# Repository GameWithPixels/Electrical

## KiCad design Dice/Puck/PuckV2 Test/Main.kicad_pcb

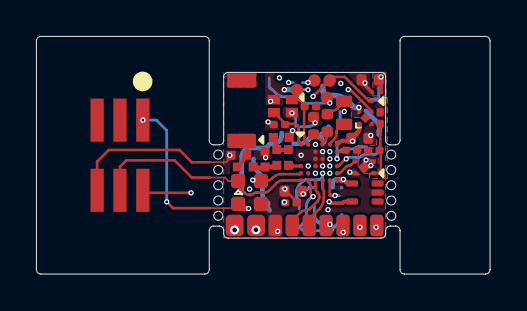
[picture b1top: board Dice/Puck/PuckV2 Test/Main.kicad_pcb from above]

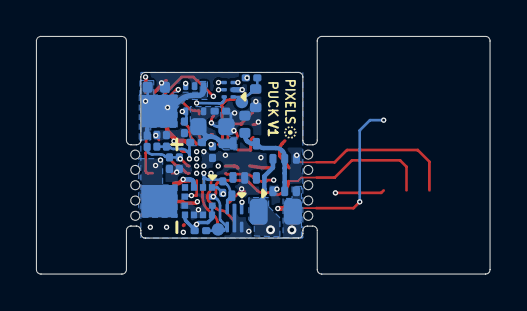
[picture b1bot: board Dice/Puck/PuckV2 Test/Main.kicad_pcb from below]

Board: 4 copper layers, 25.2 x 13.2 mm, 60 parts (28 on the bottom side), 40 nets.

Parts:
AE1: Antenna_Chip; CHIP_ANT
C1, C4, C18: 4.7uF 10V 20%; C_0402_1005Metric
C2, C5: 8pF 10V 10%; C_0201_0603Metric
C3, C10, C23: 0.1uF 10V 20%; C_0201_0603Metric
C7: 100pF NP0 10V 2%; C_0201_0603Metric
C8: 1.2pF 10V 5% C0G; 0402_RF
C9, C16: 10uF 6.3V 20%; C_0402_1005Metric
C11, C12: DNP; 0402_RF
C13: 4.7uF 25V 20%; C_0402_1005Metric
C15: 22uF 10V 20%; C_0603_1608Metric
C19: 12nF 50V 5% NP0; C_0805_2012Metric
C21, C22: 10nF 25V 10%; C_0201_0603Metric
D1: BAV99S; SOT-363_SC-70-6
J1: Conn_01x02; Batt_409090_Tabs
J2: Conn_01x04; PROG_1.27
J3: Conn_01x09; LED_CONNECTOR_9
J5: Conn_02x03_Odd_Even; PinHeader_2x03_P1.27mm_Vertical_SMD
L1: 10uH 100mA 20%; C_1.2x1.8
L2: 15nH 100mA 5%; L_0402_1005Metric
L3: 0 Ohm; 0402_RF
L4: 2.2nH 5%; 0402_RF
L5: 3.3nH 5%; 0402_RF
R1, R2, R7: 3.9M 1%; R_0201_0603Metric
R4: 10k 1%; R_0201_0603Metric
R6, R10, R11: 5.6k 1%; R_0201_0603Metric
R8: 10M 1%; R_0201_0603Metric
R9: 100k 1%; R_0201_0603Metric
R12: 510R 1%; R_0201_0603Metric
TH1: NTC 100k @ 25C; R_0402_1005Metric
U1: NRF52810-CAAA-R; WLCSP
U3: TPS715; SOT-353_SC-70-5
U4: M24C02-FMH6TG; UFDFPN5
U5: AW35122
U6: ME6230; FPB1_1-4
U7: DS6101; UDFN-4-1EP_1x1mm_P0.65mm_EP0.48x0.48mm
U8: SL1605; SOT-553
U9: XT4051; SOT-553
U10: WAS3157D-6/TR; DFN1109-6
U11: KXTJ3-1057; LGA-12_2x2mm_P0.5mm
W8: SCL; TEST_PIN
W9: SDA; TEST_PIN
W11: XC2; TEST_PIN
W15: +5V; TEST_PIN
W20: TH1; TEST_PIN
W21: LED2; TEST_PIN
W22: ADC_SELECT; TEST_PIN
W23: ADC_OUT; TEST_PIN
Y1: 32MHz 40ppm; SX16Y032000B81T001

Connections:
+5V: C15.1, R1.1, R4.1, U3.5 (VOUT), U9.5 (VCC), W15.1
+BATT: C16.1, J1.1, R7.1, R12.1, U5.A2 (VIN), U6.4 (VIN), U9.1 (BAT)
/5V_SENSE: C21.1, R1.2, R2.2, U1.D6 (P0.03/AIN1)
/ACC_INT: U1.G5 (P0.12), U11.5 (INT)
/ANTENNA: AE1.1 (FEED), C11.1, L3.2
/ANT_50: C12.1, L3.1, L5.2
/ANT_MID: C8.1, L4.2, L5.1
/ANT_NRF: L4.1, U1.E1 (ANT)
/COILA: C19.1, D1.3 (K1A2), J3.1
/COILB: C19.2, D1.6 (K3A4), J3.2
/LED_DATA: J3.4, U1.G3 (P0.16/TDATA1)
/LED_EN: U1.F3 (P0.17), U5.B2 (EN), W21.1
/LED_RETURN: J3.5, U1.G4 (P0.15)
/NTC_PHOTO_SENSE: U1.E5 (P0.04/AIN2), U10.6 (A), W23.1
/OPT_A2D: J3.8, U10.3 (B1)
/OPT_IO: J3.7, U1.F5 (P0.11)
/PROG: R6.1, U1.B5 (P0.00/XL1), U9.4 (PROG)
/SCL: R10.2, U1.G2 (P0.20/TCLK), U4.4 (SCL), U11.12 (SCL), W8.1
/SDA: R11.2, U1.F4 (P0.14), U4.3 (SDA), U11.2 (SDA), W9.1
/SENSE_SELECT: U1.E2 (P0.18/TDATA0), U10.4 (S), W22.1
/SM: U1.F6 (P0.8), U7.3 (SM)
/STATS: U1.D5 (P0.01/XL2), U9.3 (CHRG)
/VBAT_SENSE: C22.1, R7.2, R8.1, U1.E6 (P0.05/AIN3)
/Wireless Charging/B-: C23.2, J1.2, U7.2 (VSS), U7.5 (PAD)
GND: C1.2, C2.1, C3.2, C4.2, C5.1, C7.2, C8.2, C9.2, C10.2, C11.2, C12.2, C13.2, C15.2, C16.2, C18.2, C21.2, C22.2, D1.1 (A1), D1.4 (A3), J2.1, J3.3, J5.6, R2.1, R4.2, R6.2, R8.2, TH1.2, U1.B3 (VSS), U1.B4 (VSS), U1.C1 (VSS_PA), U1.D3 (VSS), U1.D4 (VSS), U1.E3 (VSS), U1.E4 (VSS), U3.2 (GND), U4.2 (VSS), U4.5 (WP), U5.B1 (GND), U6.2 (VSS), U7.4 (EB-), U8.2 (GND), U9.2 (GND), U10.2 (GND), U11.6 (GND), U11.8 (GND), U11.9 (GND), Y1.2, Y1.4
unnamed: L1.2, L2.1
unnamed: L1.1, U1.A5 (DCC)
unnamed: C3.1, U1.B6 (DEC1)
unnamed: C7.1, U1.A3 (DEC2)
unnamed: C1.1, L2.2, U1.A4 (DEC4)
unnamed: C5.2, U1.A1 (XC1), Y1.3
unnamed: C2.2, U1.A2 (XC2), W11.1, Y1.1
unnamed: U6.3 (CE), U8.5 (OUT)
unnamed: C23.1, R12.2, U7.1 (BAT)
unnamed: R9.2, TH1.1, U10.1 (B0), W20.1
SWDCLK: J2.4, J5.4, U1.G1 (SWDCLK)
SWDIO: J2.3, J5.2, U1.F1 (SWDIO)
VDC: C9.1, J3.9, R9.1, U5.A1 (VOUT), U10.5 (VCC)
VDD: C4.1, C10.1, C18.1, J2.2, J3.6, J5.1, R10.1, R11.1, U1.A6 (VDD), U1.G6 (VDD), U4.1 (VCC), U6.1 (VOUT), U8.4 (VDD), U11.1 (ADDR), U11.3 (IO_VDD), U11.7 (VDD), U11.10 (VDD), U11.11 (IO_VDD)
VEE: C13.1, D1.2 (K2), D1.5 (K4), U3.4 (VIN)

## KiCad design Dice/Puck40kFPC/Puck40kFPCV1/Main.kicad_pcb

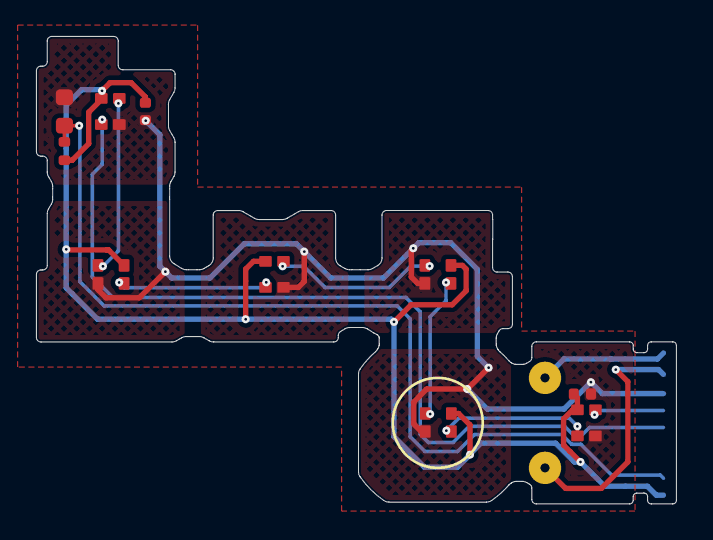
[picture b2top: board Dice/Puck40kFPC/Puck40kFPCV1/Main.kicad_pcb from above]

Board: 2 copper layers, 35.6 x 26.0 mm, 13 parts (1 on the bottom side), 12 nets.

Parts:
C10, C11: 0.1uF 10V 20%; C_0402_1005Metric
D1, D2, D3, D4, D5, D6: TX1812MJA5; TX1812MWCA5-F01
J5: Conn_01x09; LED_CONNECTOR_9
P5: COILA; TestPoint_THTPad_D1.5mm_Drill0.7mm_nosilk
P6: COILB; TestPoint_THTPad_D1.5mm_Drill0.7mm_nosilk
Q1: ZSPT-Z1608C-06F-Z4; D_0603_1608Metric
R5: 10k 1%; R_0402_1005Metric

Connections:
/COILA: J5.1, P5.1
/COILB: J5.2, P6.1
/LED_DATA: D1.3 (DIN), J5.4
/LED_RETURN: D6.1 (DOUT), J5.5
/OPT_A2D: J5.8, Q1.1 (C), R5.2
GND: C10.2, C11.2, D1.2 (GND), D2.2 (GND), D3.2 (GND), D4.2 (GND), D5.2 (GND), D6.2 (GND), J5.3, Q1.2 (E)
unnamed: D1.1 (DOUT), D2.3 (DIN)
unnamed: D2.1 (DOUT), D3.3 (DIN)
unnamed: D3.1 (DOUT), D4.3 (DIN)
unnamed: D4.1 (DOUT), D5.3 (DIN)
unnamed: D5.1 (DOUT), D6.3 (DIN)
VDC: C10.1, C11.1, D1.4 (VCC), D2.4 (VCC), D3.4 (VCC), D4.4 (VCC), D5.4 (VCC), D6.4 (VCC), J5.9, R5.1

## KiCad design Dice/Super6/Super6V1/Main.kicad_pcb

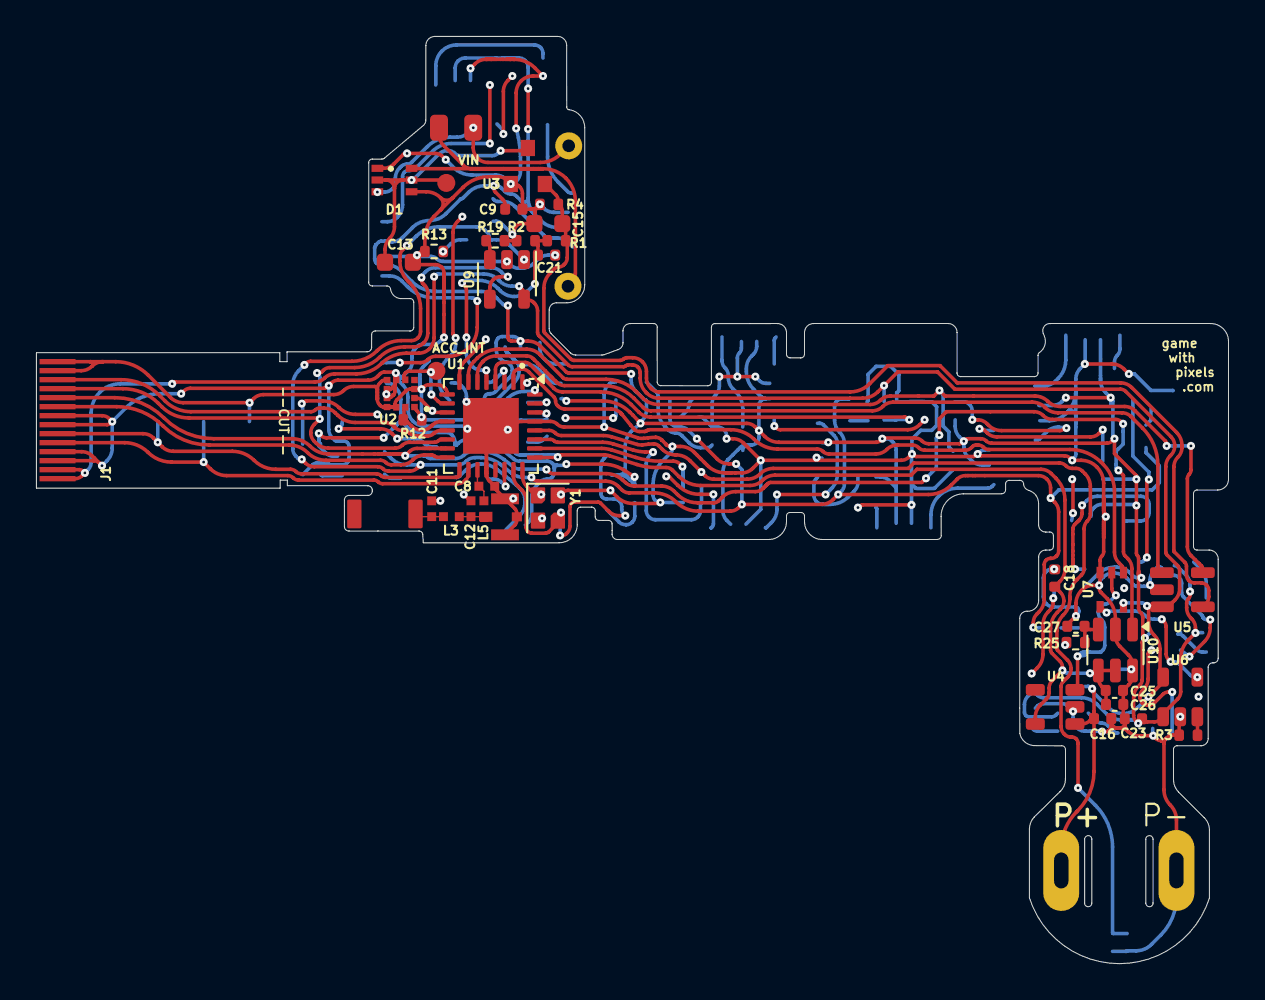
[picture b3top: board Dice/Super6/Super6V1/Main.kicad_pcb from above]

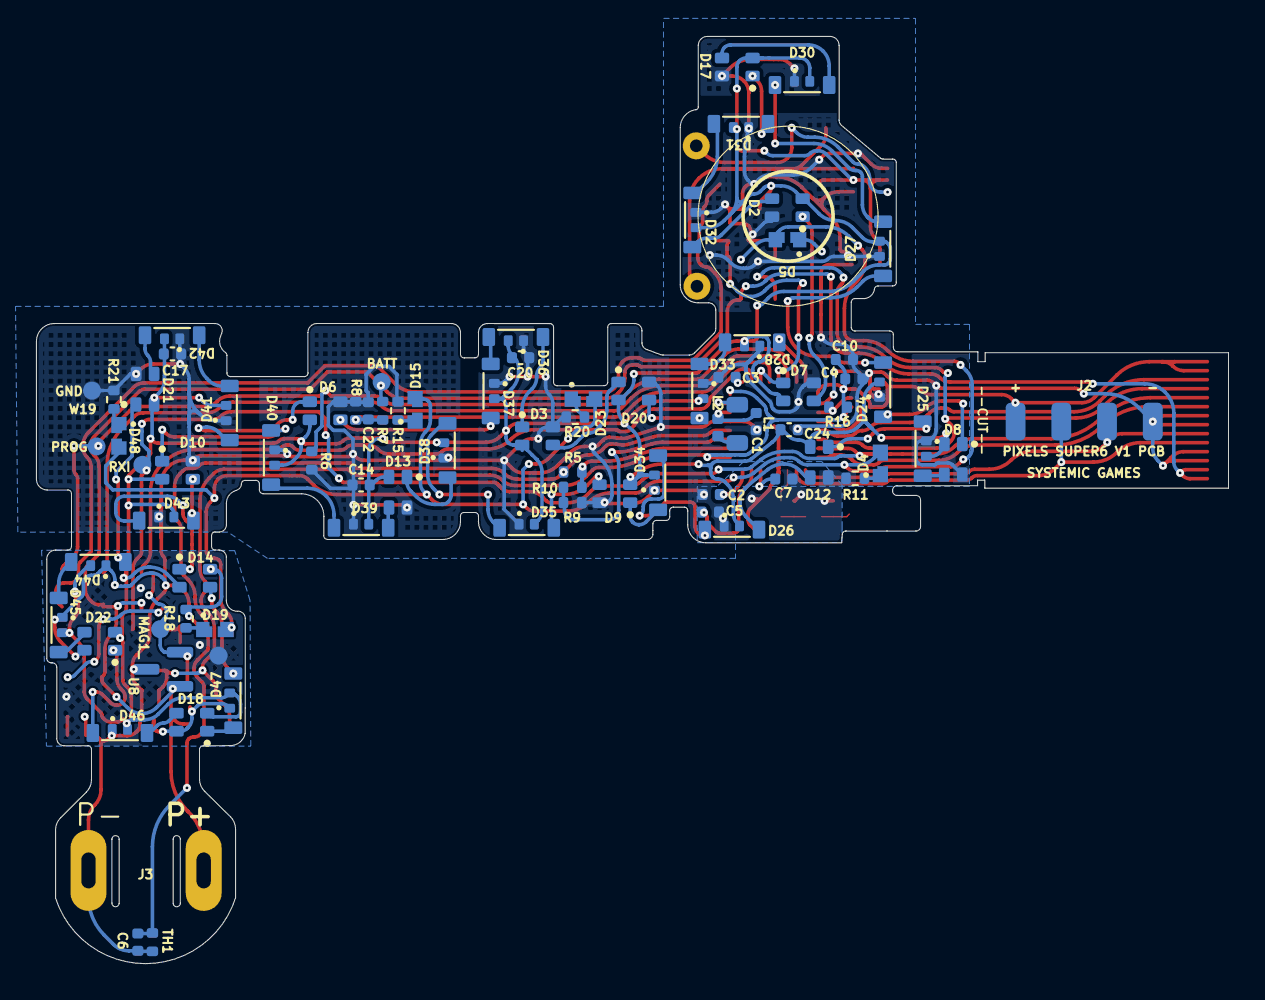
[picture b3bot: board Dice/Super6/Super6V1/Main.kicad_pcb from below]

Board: 2 copper layers, 66.2 x 51.5 mm, 123 parts (83 on the bottom side), 87 nets.

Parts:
AE2: Antenna_Chip; CHIP_ANT
C1, C4, C18: 4.7uF 10V 20%; C_0402_1005Metric
C2, C5: 8pF 10V 10%; C_0402_1005Metric
C3, C10, C14, C17, C20, C23, C24, C26: 0.1uF 10V 20%; C_0402_1005Metric
C6: DNP; C_0402_1005Metric
C7: 100pF NP0 10V 5%; C_0402_1005Metric
C8: 0.8pF 10V 5% C0G; 0402_RF
C9, C16, C25: 10uF 10V 20%; C_0402_1005Metric
C11, C12: DNP; 0402_RF
C13: 4.7uF 25V 20%; C_0603_1608Metric
C15: 22uF 10V 20%; C_0603_1608Metric
C19: 12nF 50V 5% NP0; C_0805_2012Metric
C21, C22: 10nF 25V 10%; C_0402_1005Metric
C27: 1pF 50V NP0; C_0402_1005Metric
D1: BAV99S; SOT-363_SC-70-6
D2, D3, D6, D7, D8, D9, D10, D12, D13, D14, D17, D18, D20, D21, D22: TX1812Z_2020
D4, D5, D15, D19, D23, D48: UV LED; MHP1016UVACT
D24, D25, D26, D27, D28, D30, D31, D32, D33, D34, D35, D36, D37, D38, D39, D40, D41, D42, D43, D44, D45, D46, D47: SK68XX-EC3210F
J1: Conn_01x14; FPC_14
J2: Conn_01x04; FPC-POGO-4
J3: Conn_01x02; Hongjie 10100 Connector
J4: DNP; MFH3.RECE.20369.001E.01
L1: 10uH 100mA 10%; L_0805_2012Metric
L2: 15nH 100mA 5%; L_0402_1005Metric
L3: 2.7nH 5%; 0402_RF
L5: 3.9nH 5%; 0402_RF
P5: COILA; TestPoint_THTPad_D1.5mm_Drill0.7mm_nosilk
P6: COILB; TestPoint_THTPad_D1.5mm_Drill0.7mm_nosilk
R1, R2, R7: 4.02M 1%; R_0402_1005Metric
R3, R19: 10k 5%; R_0402_1005Metric
R4, R5, R10: 100k 1%; R_0402_1005Metric
R6: 22k 1%; R_0402_1005Metric
R8: 10M 1%; R_0402_1005Metric
R9: 360k 1%; R_0402_1005Metric
R11, R13, R15, R18, R20, R21: 33R 1%; R_0402_1005Metric
R12, R16: 2.7k 5%; R_0402_1005Metric
R25: 1k 5%; R_0402_1005Metric
TH1: NTC 100k @ 25C; R_0402_1005Metric
U1: N52810_QFN32; QFN-32-1EP_5x5mm_P0.5mm_EP3.1x3.1mm
U2: KXTJ3-1057; LGA-12_2x2mm_P0.5mm
U3: PJ75BL50SA; SOT-23
U4: ME6215; SOT-23-5
U5: MCP73832T-2ACI/OT; SOT-23-5
U6, U9: MT9700; SOT-23-5
U7: SN74LVC1G08; SOT-353_SC-70-5
U8: VCS2373S; SOT-23
U10: RH6015-C; SOT-23-6
W1: RXI; TEST_PIN
W3: PROG; TEST_PIN
W6: LED_EN; TEST_PIN
W7: ACC_INT; TEST_PIN
W14: BATT; TEST_PIN
W16: VIN; TEST_PIN
W19: GND; TEST_PIN
W23: MAG1_; TEST_PIN
Y1: 32MHz 40ppm; Crystal_SMD_2016-4Pin_2.0x1.6mm

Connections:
+5V: C15.1, R1.1, R4.1, U3.2 (VOUT), U5.4 (VDD)
+BATT: C16.1, J1.1, J1.2, J3.1, R7.1, U4.1 (VIN), U5.3 (VBAT), U6.5 (VIN), U7.5 (VCC), U8.1 (VCC), U9.5 (VIN), W14.1
/5V_SENSE: C21.1, R1.2, R2.2, U1.5 (P0.05/AIN3)
/ACC_INT: U1.10 (P0.12), U2.5 (INT), W7.1
/ANTENNA: AE2.1 (FEED), C11.1, L3.2
/ANT_50: C12.1, J4.4 (RF), L3.1, L5.2
/ANT_NRF: C8.1, L5.1, U1.19 (ANT)
/BATT_NTC: C6.1, R5.2, TH1.1, U1.28 (P0.30/AIN6)
/Cap_Sense/TOUCHPAD: R25.2, W6.1
/LED_DATA: D7.1 (DIN), U1.3 (P0.01/XL2)
/LED_EN: U1.2 (P0.00/XL1), U7.1
/LEDs/LED_RETURN_6: D28.2 (DOUT), U1.8 (P0.10)
/NTC_ID_VDD: R5.1, R10.2, U1.26 (P0.25)
/PROG: R6.1, U1.7 (P0.09), U5.5 (PROG), W3.1
/Power Supply/LED_EN_OUT: U6.4 (EN), U7.4
/Power Supply/MAG1_: U4.3 (CE), U7.2, U8.2 (OUT), W23.1
/SCL: R12.2, U1.12 (P0.15), U2.12 (SCL)
/SDA: R16.2, U1.11 (P0.14), U2.2 (SDA)
/STATS: U1.6 (P0.06), U5.1 (STAT)
/UVLEDs/VUVLED: D4.2 (A), D5.2 (A), D15.2 (A), D19.2 (A), D23.2 (A), D48.2 (A), U9.1 (VOUT)
/VBAT_SENSE: C22.1, R7.2, R8.1, U1.4 (P0.04/AIN2)
GND: C1.2, C2.1, C3.2, C4.2, C5.1, C6.2, C7.2, C8.2, C9.2, C10.2, C11.2, C12.2, C13.2, C14.2, C15.2, C16.2, C17.2, C18.2, C20.2, C21.2, C22.2, C23.2, C24.2, C25.2, C26.2, C27.2, D1.1 (A1), D1.4 (A3), D2.4 (GND), D3.4 (GND), D6.4 (GND), D7.4 (GND), D8.4 (GND), D9.4 (GND), D10.4 (GND), D12.4 (GND), D13.4 (GND), D14.4 (GND), D17.4 (GND), D18.4 (GND), D20.4 (GND), D21.4 (GND), D22.4 (GND), D24.1 (GND), D25.1 (GND), D26.1 (GND), D27.1 (GND), D28.1 (GND), D30.1 (GND), D31.1 (GND), D32.1 (GND), D33.1 (GND), D34.1 (GND), D35.1 (GND), D36.1 (GND), D37.1 (GND), D38.1 (GND), D39.1 (GND), D40.1 (GND), D41.1 (GND), D42.1 (GND), D43.1 (GND), D44.1 (GND), D45.1 (GND), D46.1 (GND), D47.1 (GND), J1.3, J1.4, J1.7, J1.8, J2.4, J3.2, J4.1, J4.2, J4.3, R2.1, R3.2, R4.2, R6.2, R8.2, R9.1, R11.2, R13.2, R15.2, R18.2, R19.2, R20.2, R21.2, TH1.2, U1.20 (VSS), U1.29 (VSS), U1.33 (VSS), U2.6 (GND), U2.8 (GND), U2.9 (GND), U3.1 (VSS), U4.2 (VSS), U5.2 (VSS), U6.2 (GND), U7.3 (GND), U8.3 (GND), U9.2 (GND), U10.2 (GND), U10.6 (TOG), W19.1, Y1.2, Y1.4
unnamed: C19.2, D1.6 (K3A4), P6.1
unnamed: C19.1, D1.3 (K1A2), P5.1
unnamed: D2.1 (DIN), D7.3 (DOUT)
unnamed: D2.3 (DOUT), D32.3 (DIN)
unnamed: D3.1 (DIN), D36.2 (DOUT)
unnamed: D4.1 (K), R11.1
unnamed: D5.1 (K), R13.1
unnamed: D10.1 (DIN), D40.2 (DOUT)
unnamed: D10.3 (DOUT), D43.3 (DIN)
unnamed: D12.1 (DIN), D25.2 (DOUT)
unnamed: D12.3 (DOUT), D26.3 (DIN)
unnamed: D13.1 (DIN), D38.2 (DOUT)
unnamed: D13.3 (DOUT), D39.3 (DIN)
unnamed: D14.1 (DIN), D43.2 (DOUT)
unnamed: D14.3 (DOUT), D47.3 (DIN)
unnamed: D15.1 (K), R15.1
unnamed: D17.1 (DIN), D31.2 (DOUT)
unnamed: D17.3 (DOUT), D30.3 (DIN)
unnamed: D18.1 (DIN), D47.2 (DOUT)
unnamed: D18.3 (DOUT), D46.3 (DIN)
unnamed: D19.1 (K), R18.1
unnamed: D3.3 (DOUT), D20.1 (DIN)
unnamed: D20.3 (DOUT), D33.3 (DIN)
unnamed: D21.1 (DIN), D44.2 (DOUT)
unnamed: D21.3 (DOUT), D42.3 (DIN)
unnamed: D22.1 (DIN), D46.2 (DOUT)
unnamed: D22.3 (DOUT), D45.3 (DIN)
unnamed: D23.1 (K), R20.1
unnamed: D24.3 (DIN), D27.2 (DOUT)
unnamed: D8.1 (DIN), D24.2 (DOUT)
unnamed: D8.3 (DOUT), D25.3 (DIN)
unnamed: D26.2 (DOUT), D34.3 (DIN)
unnamed: D27.3 (DIN), D30.2 (DOUT)
unnamed: D28.3 (DIN), D33.2 (DOUT)
unnamed: D31.3 (DIN), D32.2 (DOUT)
unnamed: D9.1 (DIN), D34.2 (DOUT)
unnamed: D9.3 (DOUT), D35.3 (DIN)
unnamed: D35.2 (DOUT), D38.3 (DIN)
unnamed: D36.3 (DIN), D37.2 (DOUT)
unnamed: D6.3 (DOUT), D37.3 (DIN)
unnamed: D39.2 (DOUT), D40.3 (DIN)
unnamed: D41.3 (DIN), D42.2 (DOUT)
unnamed: D6.1 (DIN), D41.2 (DOUT)
unnamed: D44.3 (DIN), D45.2 (DOUT)
unnamed: D48.1 (K), R21.1
unnamed: L1.2, L2.1
unnamed: L1.1, U1.31 (DCC)
unnamed: C3.1, U1.1 (DEC1)
unnamed: C7.1, U1.22 (DEC3)
unnamed: C1.1, L2.2, U1.30 (DEC4)
unnamed: R9.2, R10.1, U1.27 (P0.28/AIN4)
unnamed: C5.2, U1.23 (XC1), Y1.3
unnamed: C2.2, U1.24 (XC2), Y1.1
unnamed: R3.1, U6.3 (SET)
unnamed: R19.1, U9.3 (SET)
unnamed: C27.1, R25.1, U10.3 (TCH)
RESET: J1.9, U1.16 (P0.16)
RXI: J1.10, U1.15 (P0.20/TCLK), U10.1 (OC), W1.1
SWDCLK: J1.6, J2.3, U1.17 (SWDCLK)
SWDIO: J1.5, J2.2, U1.18 (SWDIO)
SWO: J1.11, U1.14 (P0.18/TDATA0), U9.4 (EN)
TXO: J1.12, U1.13 (P0.16/TDATA1)
VDC: C9.1, C14.1, C17.1, C20.1, C23.1, C24.1, D2.2 (VCC), D3.2 (VCC), D6.2 (VCC), D7.2 (VCC), D8.2 (VCC), D9.2 (VCC), D10.2 (VCC), D12.2 (VCC), D13.2 (VCC), D14.2 (VCC), D17.2 (VCC), D18.2 (VCC), D20.2 (VCC), D21.2 (VCC), D22.2 (VCC), D24.4 (VCC), D25.4 (VCC), D26.4 (VCC), D27.4 (VCC), D28.4 (VCC), D30.4 (VCC), D31.4 (VCC), D32.4 (VCC), D33.4 (VCC), D34.4 (VCC), D35.4 (VCC), D36.4 (VCC), D37.4 (VCC), D38.4 (VCC), D39.4 (VCC), D40.4 (VCC), D41.4 (VCC), D42.4 (VCC), D43.4 (VCC), D44.4 (VCC), D45.4 (VCC), D46.4 (VCC), D47.4 (VCC), U6.1 (VOUT)
VDD: C4.1, C10.1, C18.1, C25.1, C26.1, J1.13, J1.14, J2.1, R12.1, R16.1, U1.9 (VDD), U1.25 (VDD), U1.32 (VDD), U2.1 (ADDR), U2.3 (IO_VDD), U2.7 (VDD), U2.10 (VDD), U2.11 (IO_VDD), U4.5 (VOUT), U10.4 (AHLB), U10.5 (VDD)
VEE: C13.1, D1.2 (K2), D1.5 (K4), U3.3 (VIN), W16.1

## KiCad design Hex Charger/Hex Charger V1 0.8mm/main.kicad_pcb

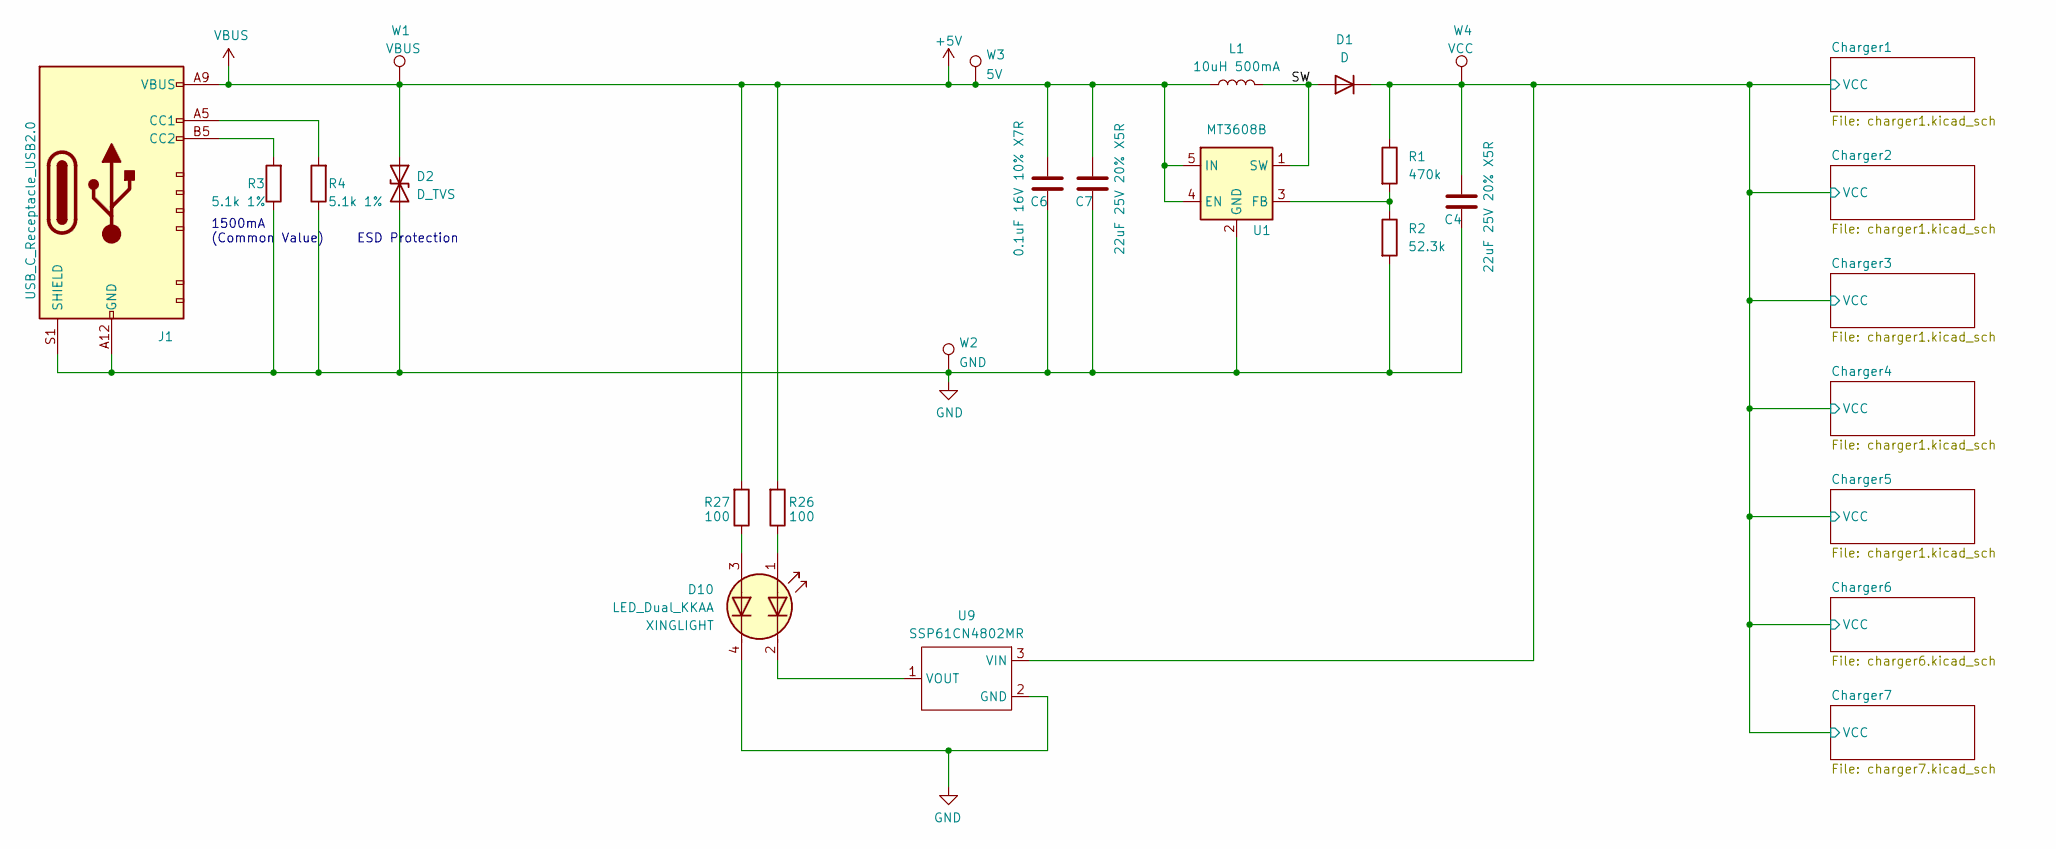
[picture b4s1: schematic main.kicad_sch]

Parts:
C4, C7: 22uF 25V 20% X5R; C_0805_2012Metric; Part Number GRM21BR61E226ME44L; LCSC Part # C86816
C6: 0.1uF 16V 10% X7R; C_0603_1608Metric; Part Number CL10B104KO8NNNC; LCSC Part # C66501
D1: D; SMAF; Part Number SS54F; LCSC Part # C908671
D2: D_TVS; DFN; Part Number LXES1UTAA1-157; LCSC Part # C5210979
D10: LED_Dual_KKAA; XL-3210SURUGC; Part Number XL-3210SURUGC; LCSC Part # C965883
J1: USB_C_Receptacle_USB2.0; USB-C-SMD_10P-P1.00-L6.8-W8.9; Part Number TYPE-C-31-M-17; LCSC Part # C283540
L1: 10uH 500mA; L_Wuerth_HCM-7050; Part Number RS0650-100MS; LCSC Part # C32712977
R1: 470k; R_0402_1005Metric; Part Number 0402WGF4703TCE; LCSC Part # C25790
R2: 52.3k; R_0402_1005Metric; Part Number 0402WGF5232TCE; LCSC Part # C26982
R3, R4: 5.1k 1%; R_0402_1005Metric; Part Number 0402WGF5101TCE; LCSC Part # C25905
R26, R27: 100; R_0402_1005Metric; Part Number 0402WGF1000TCE; LCSC Part # C25076
U1: MT3608B; SOT-23-6; Part Number MT3608B; LCSC Part # C19189893
U9: SSP61CN4802MR; SOT-23; Part Number HT7050S; LCSC Part # C2842953
W1: VBUS; TestPoint_1.5x1.5_Drill0.9mm
W2: GND; TestPoint_1.5x1.5_Drill0.9mm
W3: 5V; TestPoint_1.5x1.5_Drill0.9mm
W4: VCC; TestPoint_1.5x1.5_Drill0.9mm

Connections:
+5V: C6.1, C7.1, D2.1 (A1), J1.A9 (VBUS), J1.B9 (VBUS), L1.1, R26.2, R27.2, U1.4 (EN), U1.5 (IN), W1.1, W3.1
/Charger1/VCC: C4.1, D1.1 (K), R1.1, U9.3 (VIN), W4.1; also elsewhere on the board
/SW: D1.2 (A), L1.2, U1.1 (SW)
GND: C4.2, C6.2, C7.2, D2.2 (A2), D10.4 (K2), J1.A12 (GND), J1.B12 (GND), J1.S1 (SHIELD), R2.2, R3.1, R4.1, U1.2 (GND), U9.2 (GND), W2.1; also elsewhere on the board
unnamed: D10.1 (A1), R26.1
unnamed: D10.3 (A2), R27.1
unnamed: D10.2 (K1), U9.1 (VOUT)
unnamed: J1.A5 (CC1), R4.2
unnamed: J1.B5 (CC2), R3.2
unnamed: R1.2, R2.1, U1.3 (FB)

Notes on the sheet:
1500mA (Common Value)
ESD Protection

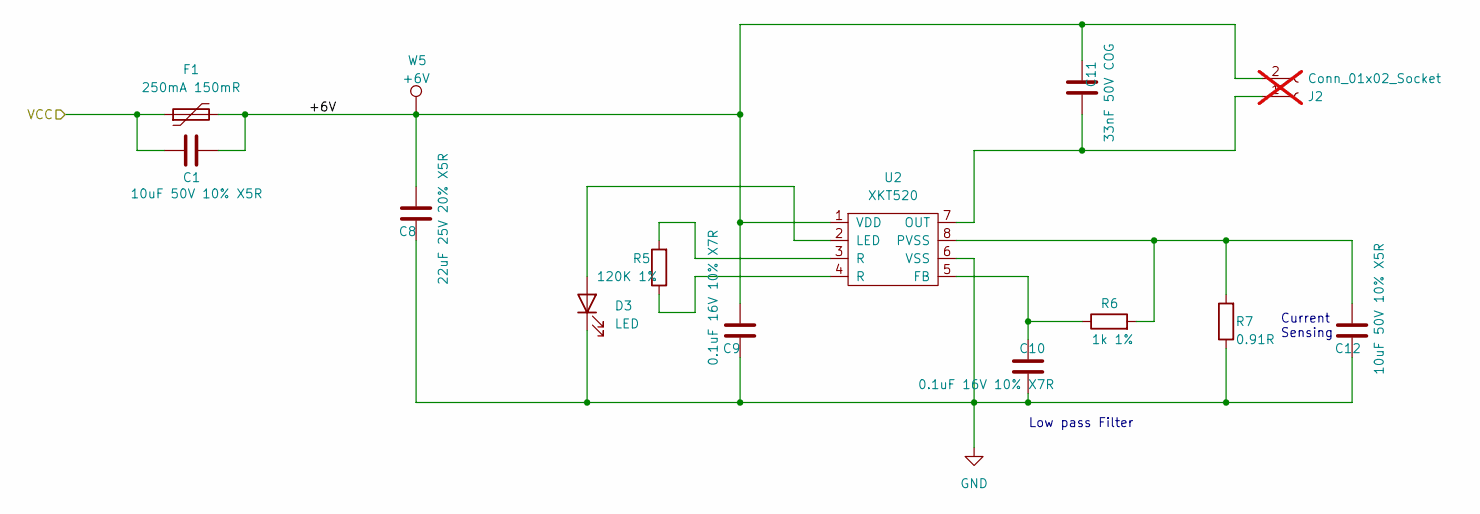
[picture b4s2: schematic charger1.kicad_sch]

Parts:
C1, C12: 10uF 50V 10% X5R; C_0805_2012Metric; Part Number GRM21BR61H106KE43L; LCSC Part # C440198
C8: 22uF 25V 20% X5R; C_0805_2012Metric; Part Number GRM21BR61E226ME44L; LCSC Part # C86816
C9, C10: 0.1uF 16V 10% X7R; C_0603_1608Metric; Part Number CL10B104KO8NNNC; LCSC Part # C66501
C11: 33nF 50V COG; C_1206_3216Metric; Part Number GRM3195C1H333JA01D; LCSC Part # C97930
D3: LED; LED_0603_1608Metric; Part Number LTST-C191KRKT; LCSC Part # C125099
F1: 250mA 150mR; Fuse_1206_3216Metric; Part Number BSMD1206-025-33V; LCSC Part # C2977524
J2: Conn_01x02_Socket; COIL_215_10T_055_020; not fitted
R5: 120K 1%; R_0402_1005Metric; Part Number 0402WGF1203TCE; LCSC Part # C25750
R6: 1k 1%; R_0402_1005Metric; Part Number 0402WGF1001TCE; LCSC Part # C11702
R7: 0.91R; R_1206_3216Metric; Part Number RL1206FR-7W0R91L; LCSC Part # C136987
U2: XKT520; SOIC-8_3.9x4.9mm_P1.27mm
W5: +6V; TestPoint_1.5x1.5_Drill0.9mm

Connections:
/Charger1/+6V: C1.1, C8.1, C9.1, C11.2, F1.2, J2.2, U2.1 (VDD), W5.1
/Charger1/VCC: C1.2, F1.1; also elsewhere on the board
GND: C8.2, C9.2, C10.1, C12.2, D3.1 (K), R7.1, U2.6 (VSS); also elsewhere on the board
unnamed: D3.2 (A), U2.2 (LED)
unnamed: C11.1, J2.1, U2.7 (OUT)
unnamed: R5.1, U2.4 (R)
unnamed: R5.2, U2.3 (R)
unnamed: C10.2, R6.1, U2.5 (FB)
unnamed: C12.1, R6.2, R7.2, U2.8 (PVSS)

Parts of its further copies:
C2, C3, C5, C17, C26, C27, C32, C43: 10uF 50V 10% X5R; C_0805_2012Metric; Part Number GRM21BR61H106KE43L; LCSC Part # C440198
C13, C18, C19, C28: 22uF 25V 20% X5R; C_0805_2012Metric; Part Number GRM21BR61E226ME44L; LCSC Part # C86816
C14, C15, C20, C21, C22, C23, C29, C30: 0.1uF 16V 10% X7R; C_0603_1608Metric; Part Number CL10B104KO8NNNC; LCSC Part # C66501
C16, C24, C25, C31: 33nF 50V COG; C_1206_3216Metric; Part Number GRM3195C1H333JA01D; LCSC Part # C97930
D4, D5, D6, D7: LED; LED_0603_1608Metric; Part Number LTST-C191KRKT; LCSC Part # C125099
F2, F3, F4, F5: 250mA 150mR; Fuse_1206_3216Metric; Part Number BSMD1206-025-33V; LCSC Part # C2977524
J3, J4, J5, J6: Conn_01x02_Socket; COIL_215_10T_055_020; not fitted
R8, R11, R12, R17: 120K 1%; R_0402_1005Metric; Part Number 0402WGF1203TCE; LCSC Part # C25750
R9, R13, R14, R18: 1k 1%; R_0402_1005Metric; Part Number 0402WGF1001TCE; LCSC Part # C11702
R10, R15, R16, R19: 0.91R; R_1206_3216Metric; Part Number RL1206FR-7W0R91L; LCSC Part # C136987
U3, U4, U5, U6: XKT520; SOIC-8_3.9x4.9mm_P1.27mm
W6, W7, W8, W9: +6V; TestPoint_1.5x1.5_Drill0.9mm

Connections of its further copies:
/Charger1/VCC: C2.2, C3.2, C5.2, C43.2, F2.1, F3.1, F4.1, F5.1; also elsewhere on the board
/Charger2/+6V: C2.1, C13.1, C14.1, C16.2, F2.2, J3.2, U3.1 (VDD), W6.1
/Charger3/+6V: C3.1, C18.1, C20.1, C24.2, F3.2, J4.2, U4.1 (VDD), W7.1
/Charger4/+6V: C5.1, C19.1, C21.1, C25.2, F4.2, J5.2, U5.1 (VDD), W8.1
/Charger5/+6V: C28.1, C29.1, C31.2, C43.1, F5.2, J6.2, U6.1 (VDD), W9.1
GND: C13.2, C14.2, C15.1, C17.2, C18.2, C19.2, C20.2, C21.2, C22.1, C23.1, C26.2, C27.2, C28.2, C29.2, C30.1, C32.2, D4.1 (K), D5.1 (K), D6.1 (K), D7.1 (K), R10.1, R15.1, R16.1, R19.1, U3.6 (VSS), U4.6 (VSS), U5.6 (VSS), U6.6 (VSS); also elsewhere on the board
unnamed: D4.2 (A), U3.2 (LED)
unnamed: D5.2 (A), U4.2 (LED)
unnamed: D6.2 (A), U5.2 (LED)
unnamed: D7.2 (A), U6.2 (LED)
unnamed: C16.1, J3.1, U3.7 (OUT)
unnamed: C24.1, J4.1, U4.7 (OUT)
unnamed: C25.1, J5.1, U5.7 (OUT)
unnamed: C31.1, J6.1, U6.7 (OUT)
unnamed: R8.1, U3.4 (R)
unnamed: R8.2, U3.3 (R)
unnamed: R11.1, U4.4 (R)
unnamed: R11.2, U4.3 (R)
unnamed: R12.1, U5.4 (R)
unnamed: R12.2, U5.3 (R)
unnamed: R17.1, U6.4 (R)
unnamed: R17.2, U6.3 (R)
unnamed: C15.2, R9.1, U3.5 (FB)
unnamed: C17.1, R9.2, R10.2, U3.8 (PVSS)
unnamed: C22.2, R13.1, U4.5 (FB)
unnamed: C26.1, R13.2, R15.2, U4.8 (PVSS)
unnamed: C23.2, R14.1, U5.5 (FB)
unnamed: C27.1, R14.2, R16.2, U5.8 (PVSS)
unnamed: C30.2, R18.1, U6.5 (FB)
unnamed: C32.1, R18.2, R19.2, U6.8 (PVSS)

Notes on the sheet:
Current Sensing
Low pass Filter

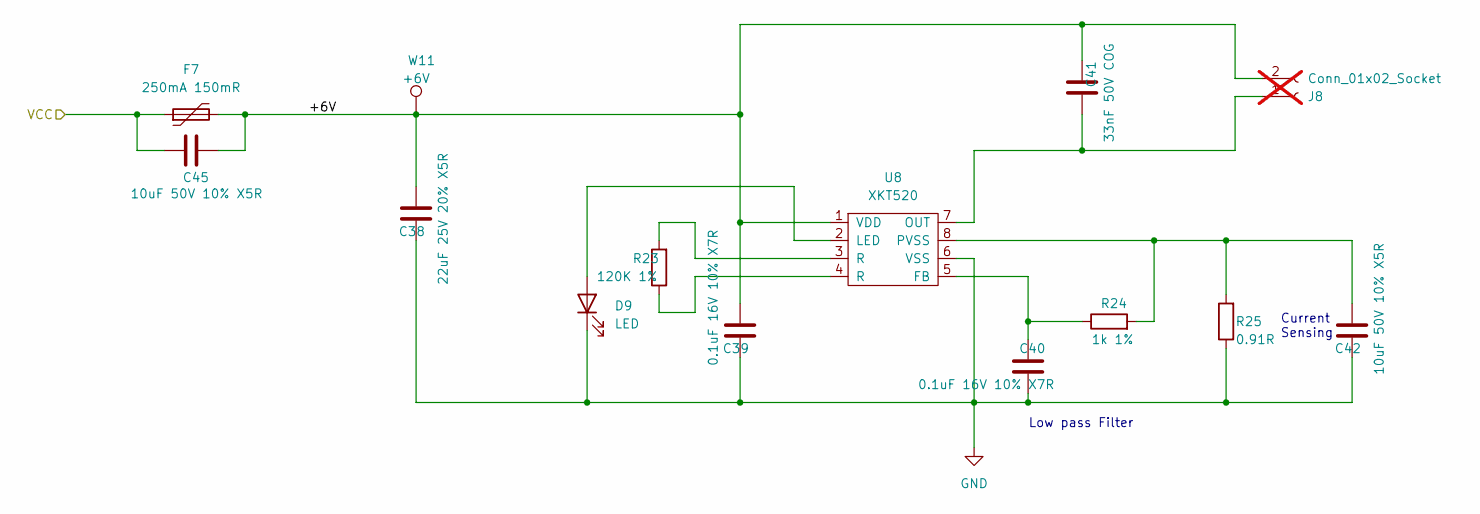
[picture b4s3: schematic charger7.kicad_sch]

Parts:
C38: 22uF 25V 20% X5R; C_0805_2012Metric; Part Number GRM21BR61E226ME44L; LCSC Part # C86816
C39, C40: 0.1uF 16V 10% X7R; C_0603_1608Metric; Part Number CL10B104KO8NNNC; LCSC Part # C66501
C41: 33nF 50V COG; C_1206_3216Metric; Part Number GRM3195C1H333JA01D; LCSC Part # C97930
C42, C45: 10uF 50V 10% X5R; C_0805_2012Metric; Part Number GRM21BR61H106KE43L; LCSC Part # C440198
D9: LED; LED_0603_1608Metric; Part Number LTST-C191KRKT; LCSC Part # C125099
F7: 250mA 150mR; Fuse_1206_3216Metric; Part Number BSMD1206-025-33V; LCSC Part # C2977524
J8: Conn_01x02_Socket; COIL_205_10T_055_020; not fitted
R23: 120K 1%; R_0402_1005Metric; Part Number 0402WGF1203TCE; LCSC Part # C25750
R24: 1k 1%; R_0402_1005Metric; Part Number 0402WGF1001TCE; LCSC Part # C11702
R25: 0.91R; R_1206_3216Metric; Part Number RL1206FR-7W0R91L; LCSC Part # C136987
U8: XKT520; SOIC-8_3.9x4.9mm_P1.27mm
W11: +6V; TestPoint_1.5x1.5_Drill0.9mm

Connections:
/Charger1/VCC: C45.2, F7.1; also elsewhere on the board
/Charger7/+6V: C38.1, C39.1, C41.2, C45.1, F7.2, J8.2, U8.1 (VDD), W11.1
GND: C38.2, C39.2, C40.1, C42.2, D9.1 (K), R25.1, U8.6 (VSS); also elsewhere on the board
unnamed: D9.2 (A), U8.2 (LED)
unnamed: C41.1, J8.1, U8.7 (OUT)
unnamed: R23.1, U8.4 (R)
unnamed: R23.2, U8.3 (R)
unnamed: C40.2, R24.1, U8.5 (FB)
unnamed: C42.1, R24.2, R25.2, U8.8 (PVSS)

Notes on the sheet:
Current Sensing
Low pass Filter

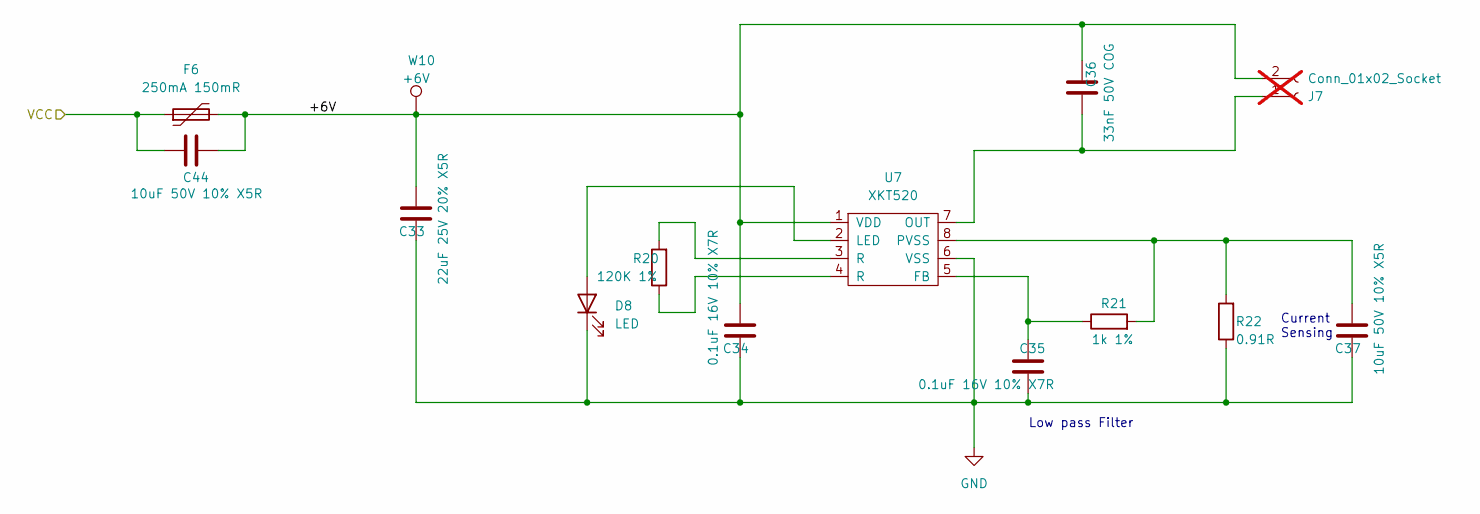
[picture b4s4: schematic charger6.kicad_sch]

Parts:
C33: 22uF 25V 20% X5R; C_0805_2012Metric; Part Number GRM21BR61E226ME44L; LCSC Part # C86816
C34, C35: 0.1uF 16V 10% X7R; C_0603_1608Metric; Part Number CL10B104KO8NNNC; LCSC Part # C66501
C36: 33nF 50V COG; C_1206_3216Metric; Part Number GRM3195C1H333JA01D; LCSC Part # C97930
C37, C44: 10uF 50V 10% X5R; C_0805_2012Metric; Part Number GRM21BR61H106KE43L; LCSC Part # C440198
D8: LED; LED_0603_1608Metric; Part Number LTST-C191KRKT; LCSC Part # C125099
F6: 250mA 150mR; Fuse_1206_3216Metric; Part Number BSMD1206-025-33V; LCSC Part # C2977524
J7: Conn_01x02_Socket; COIL_210_10T_055_020; not fitted
R20: 120K 1%; R_0402_1005Metric; Part Number 0402WGF1203TCE; LCSC Part # C25750
R21: 1k 1%; R_0402_1005Metric; Part Number 0402WGF1001TCE; LCSC Part # C11702
R22: 0.91R; R_1206_3216Metric; Part Number RL1206FR-7W0R91L; LCSC Part # C136987
U7: XKT520; SOIC-8_3.9x4.9mm_P1.27mm
W10: +6V; TestPoint_1.5x1.5_Drill0.9mm

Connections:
/Charger1/VCC: C44.2, F6.1; also elsewhere on the board
/Charger6/+6V: C33.1, C34.1, C36.2, C44.1, F6.2, J7.2, U7.1 (VDD), W10.1
GND: C33.2, C34.2, C35.1, C37.2, D8.1 (K), R22.1, U7.6 (VSS); also elsewhere on the board
unnamed: D8.2 (A), U7.2 (LED)
unnamed: C36.1, J7.1, U7.7 (OUT)
unnamed: R20.1, U7.4 (R)
unnamed: R20.2, U7.3 (R)
unnamed: C35.2, R21.1, U7.5 (FB)
unnamed: C37.1, R21.2, R22.2, U7.8 (PVSS)

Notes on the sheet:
Current Sensing
Low pass Filter
